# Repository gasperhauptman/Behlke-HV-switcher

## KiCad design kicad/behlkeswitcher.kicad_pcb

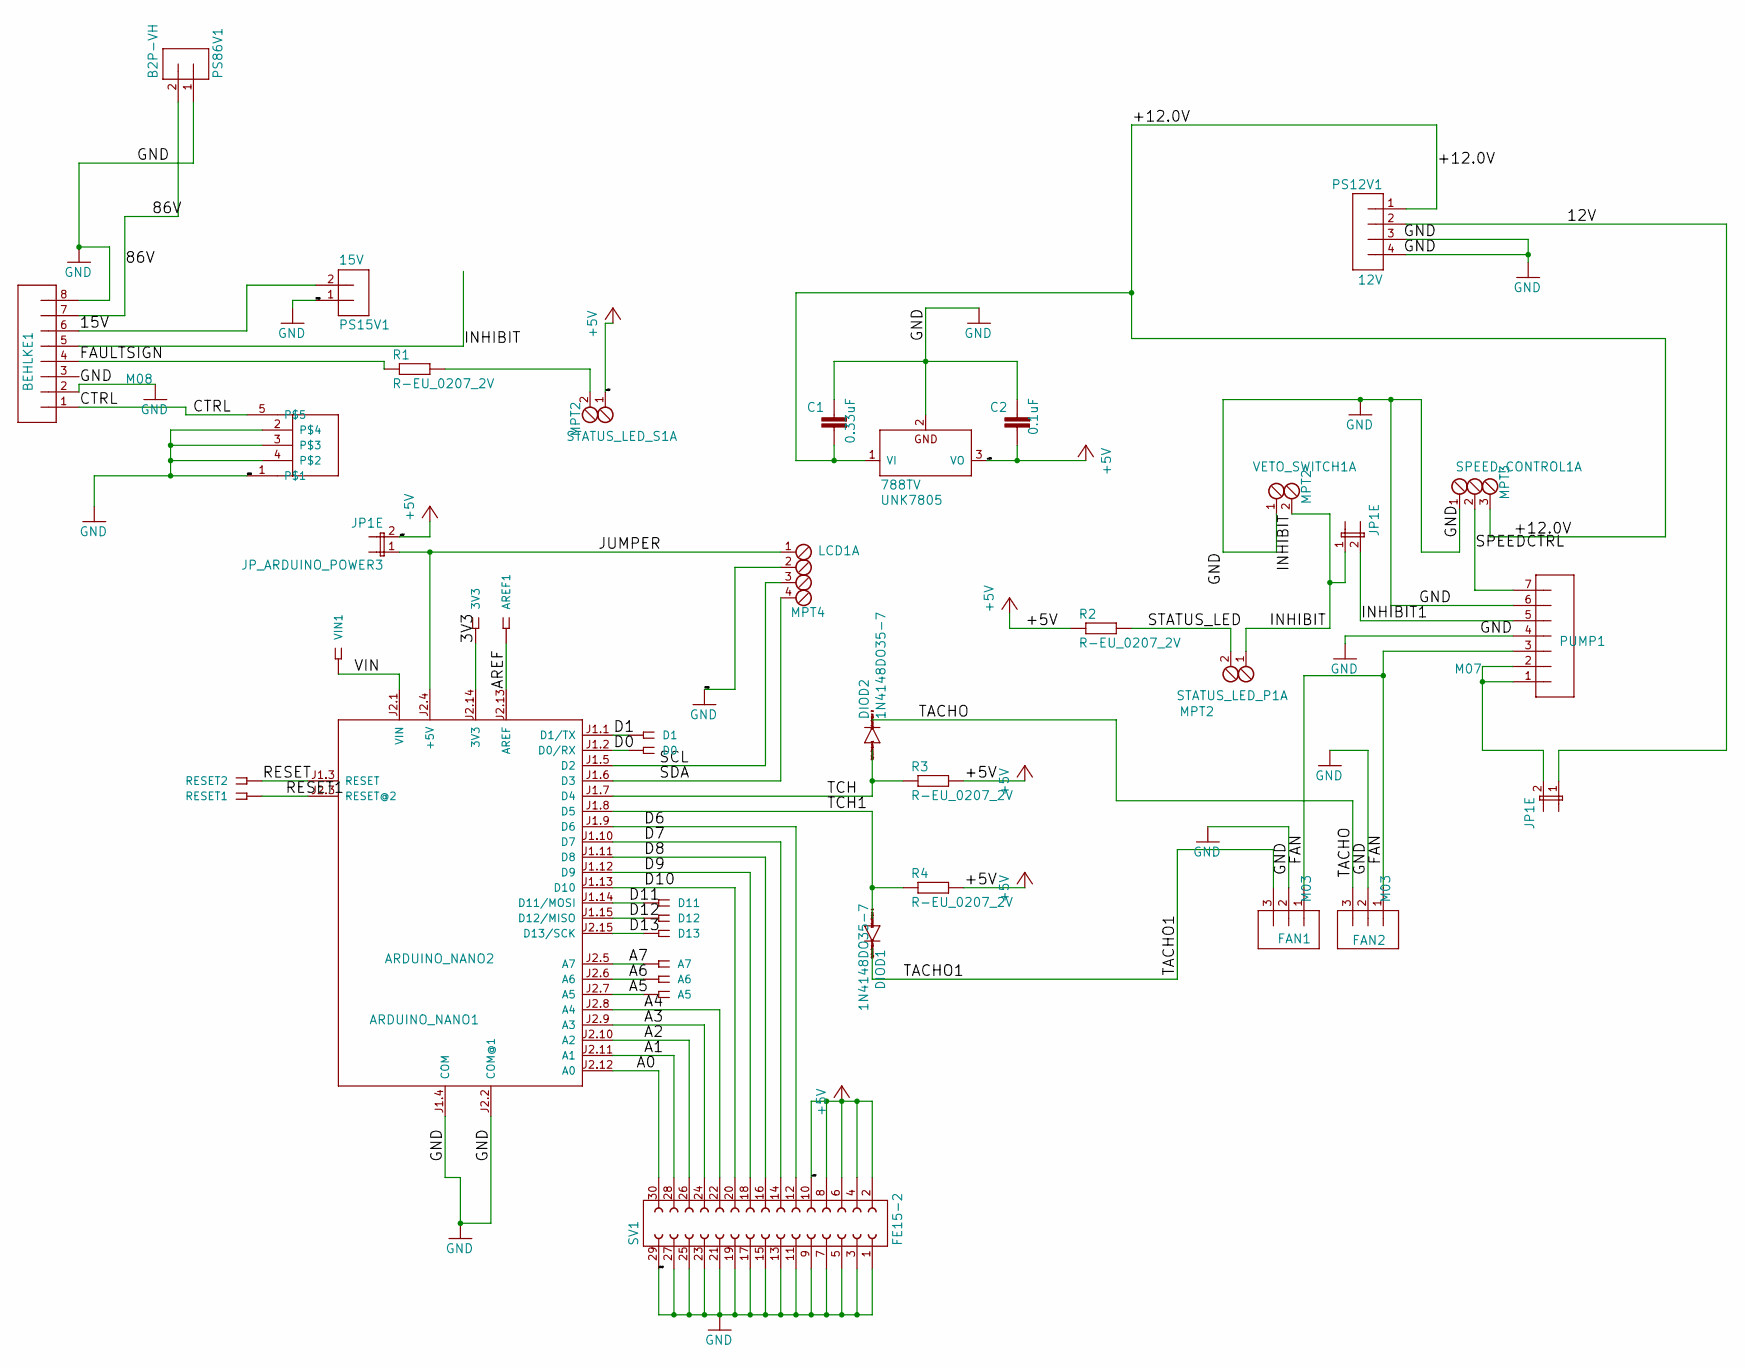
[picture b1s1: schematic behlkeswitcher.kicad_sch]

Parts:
3V3: SSW-101-02-G-S
A5, A6, A7: SSW-101-02-G-S
ARDUINO_NANO1: ARDUINO_NANO2
AREF1: SSW-101-02-G-S
BEHLKE1: M08; 08P
C1: 0.33uF; C2.5-3
C2: 0.1uF; C2.5-3
COAX1: 5-1634506-1
D0, D1, D11, D12, D13: SSW-101-02-G-S
DIOD1, DIOD2: 1N4148DO35-7; DO35-7
FAN1, FAN2: M03; 03P
JP_ARDUINO_POWER1, JP_ARDUINO_POWER2, JP_ARDUINO_POWER3: JP1E; JP1
LCD1: MPT4; 4POL254
PS12V1: 12V; B4P-VH
PS15V1: 15V; B2P-VH
PS86V1: B2P-VH
PUMP1: M07; 07P
R1, R2, R3, R4: R-EU_0207_2V; 0207_2V
RESET1, RESET2: SSW-101-02-G-S
SPEED_CONTROL1: MPT3; 3POL254
STATUS_LED_P1: MPT2; 2POL254
STATUS_LED_S1: MPT2; 2POL254
SV1: FE15-2
UNK7805: 788TV; TO220V
VETO_SWITCH1: MPT2; 2POL254
VIN1: SSW-101-02-G-S

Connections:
+5V: C2.2, JP_ARDUINO_POWER3.2, R2.1, R3.2, R4.2, STATUS_LED_S1.1, SV1.2, SV1.4, SV1.6, SV1.8, SV1.10, UNK7805.3 (VO)
/3V3: 3V3.1, ARDUINO_NANO1.J2.14 (3V3)
/12V: JP_ARDUINO_POWER2.1, PS12V1.2
/15V: BEHLKE1.6, PS15V1.2
/86V: BEHLKE1.7, PS86V1.2
/+12.0V: C1.2, PS12V1.1, SPEED_CONTROL1.3, UNK7805.1 (VI)
/A0: ARDUINO_NANO1.J2.12 (A0), SV1.30
/A1: ARDUINO_NANO1.J2.11 (A1), SV1.28
/A2: ARDUINO_NANO1.J2.10 (A2), SV1.26
/A3: ARDUINO_NANO1.J2.9 (A3), SV1.24
/A4: ARDUINO_NANO1.J2.8 (A4), SV1.22
/A5: A5.1, ARDUINO_NANO1.J2.7 (A5)
/A6: A6.1, ARDUINO_NANO1.J2.6 (A6)
/A7: A7.1, ARDUINO_NANO1.J2.5 (A7)
/AREF: ARDUINO_NANO1.J2.13 (AREF), AREF1.1
/CTRL: BEHLKE1.1, COAX1.5
/D0: ARDUINO_NANO1.J1.2 (D0/RX), D0.1
/D1: ARDUINO_NANO1.J1.1 (D1/TX), D1.1
/D6: ARDUINO_NANO1.J1.9 (D6), SV1.12
/D7: ARDUINO_NANO1.J1.10 (D7), SV1.14
/D8: ARDUINO_NANO1.J1.11 (D8), SV1.16
/D9: ARDUINO_NANO1.J1.12 (D9), SV1.18
/D10: ARDUINO_NANO1.J1.13 (D10), SV1.20
/D11: ARDUINO_NANO1.J1.14 (D11/MOSI), D11.1
/D12: ARDUINO_NANO1.J1.15 (D12/MISO), D12.1
/D13: ARDUINO_NANO1.J2.15 (D13/SCK), D13.1
/FAN: FAN1.1, FAN2.1, PUMP1.3
/FAULTSIGN: BEHLKE1.4, R1.1
/INHIBIT: BEHLKE1.5, JP_ARDUINO_POWER1.1, STATUS_LED_P1.1, VETO_SWITCH1.2
/INHIBIT1: JP_ARDUINO_POWER1.2, PUMP1.5
/JUMPER: ARDUINO_NANO1.J2.4 (+5V), JP_ARDUINO_POWER3.1, LCD1.1
/RESET: ARDUINO_NANO1.J1.3 (RESET), RESET2.1
/RESET1: ARDUINO_NANO1.J2.3 (RESET@2), RESET1.1
/SCL: ARDUINO_NANO1.J1.5 (D2), LCD1.3
/SDA: ARDUINO_NANO1.J1.6 (D3), LCD1.4
/SPEEDCTRL: PUMP1.7, SPEED_CONTROL1.2
/STATUS_LED: R2.2, STATUS_LED_P1.2
/TACHO: DIOD2.C, FAN2.3
/TACHO1: DIOD1.C, FAN1.3
/TCH: ARDUINO_NANO1.J1.7 (D4), DIOD2.A, R3.1
/TCH1: ARDUINO_NANO1.J1.8 (D5), DIOD1.A, R4.1
/VIN: ARDUINO_NANO1.J2.1 (VIN), VIN1.1
GND: ARDUINO_NANO1.J1.4 (COM), ARDUINO_NANO1.J2.2 (COM@1), BEHLKE1.2, BEHLKE1.8, C1.1, C2.1, COAX1.1, COAX1.2, COAX1.3, COAX1.4, FAN1.2, FAN2.2, LCD1.2, PS12V1.3, PS12V1.4, PS15V1.1, PS86V1.1, PUMP1.4, PUMP1.6, SPEED_CONTROL1.1, SV1.1, SV1.3, SV1.5, SV1.7, SV1.9, SV1.11, SV1.13, SV1.15, SV1.17, SV1.19, SV1.21, SV1.23, SV1.25, SV1.27, SV1.29, UNK7805.2 (GND), VETO_SWITCH1.1
unnamed: JP_ARDUINO_POWER2.2, PUMP1.1, PUMP1.2
unnamed: R1.2, STATUS_LED_S1.2

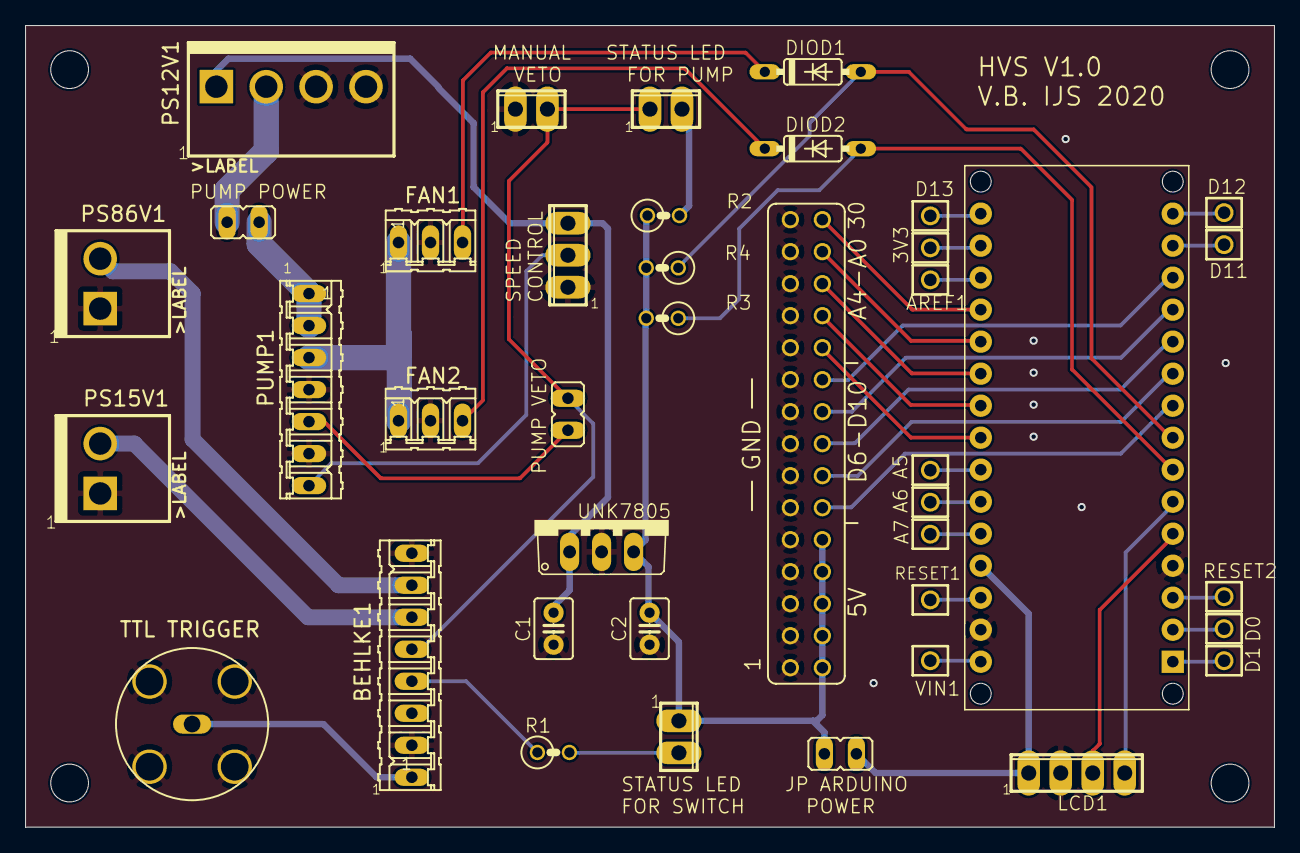
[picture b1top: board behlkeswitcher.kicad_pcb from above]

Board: 2 copper layers, 99.1 x 63.6 mm, 44 parts (0 on the bottom side), 45 nets.

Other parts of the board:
@HOLE0, @HOLE1, @HOLE2, @HOLE3: (no value)
